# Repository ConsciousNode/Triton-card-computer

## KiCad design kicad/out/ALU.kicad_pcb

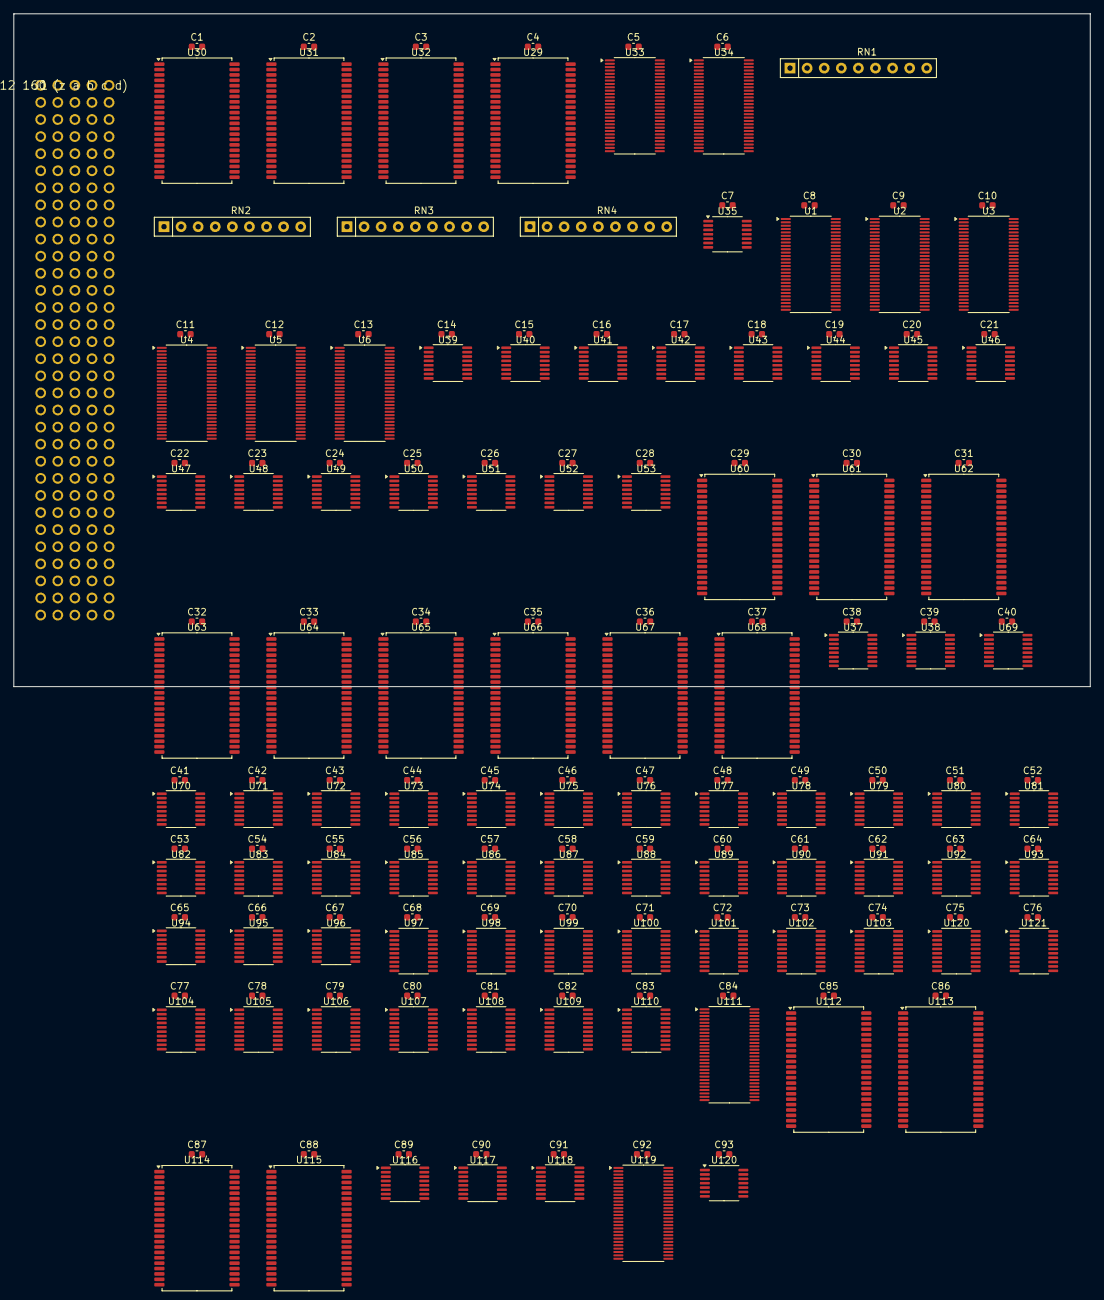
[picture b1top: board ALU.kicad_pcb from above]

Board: 4 copper layers, 160.0 x 100.0 mm, 191 parts (0 on the bottom side), 470 nets, no tracks yet.

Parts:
C1, C2, C3, C4, C5, C6, C7, C8, C9, C10, C11, C12, C13, C14, C15, C16, C17, C18, C19, C20, C21, C22, C23, C24, C25, C26, C27, C28, C29, C30, C31, C32, C33, C34, C35, C36, C37, C38, C39, C40, C41, C42, C43, C44, C45, C46, C47, C48, C49, C50, C51, C52, C53, C54, C55, C56, C57, C58, C59, C60, C61, C62, C63, C64, C65, C66, C67, C68, C69, C70, C71, C72, C73, C74, C75, C76, C77, C78, C79, C80, C81, C82, C83, C84, C85, C86, C87, C88, C89, C90, C91, C92, C93: 100n; C_0603_1608Metric
J1: DIN41612 160 (z a b c d)
RN1, RN2, RN3, RN4: RPACK8; R_Array_SIP9
U1, U2, U3, U4, U5, U6, U33, U34, U111, U119: ALVCH16823; TSSOP-56_6.1x14mm_P0.5mm
U29, U30, U31, U32, U60, U61, U62, U63, U64, U65, U66, U67, U68, U112, U113, U114, U115: IS61WV5128; TSOP-II-44_10.16x18.41mm_P0.8mm
U35: LVC32; TSSOP-14_4.4x5mm_P0.65mm
U37, U39, U40, U69, U116, U117, U118: LVC153; TSSOP-16_4.4x5mm_P0.65mm
U38, U41, U42, U43, U44, U45, U46, U47, U48, U49, U50, U51, U52, U53: LVC157; TSSOP-16_4.4x5mm_P0.65mm
U70, U71, U72, U73, U74, U75, U76, U77, U78, U79, U80, U81, U82, U83, U84, U85, U86, U87, U88, U89, U90, U91, U92, U93, U94, U95, U96: CBTLV3253; TSSOP-16_4.4x5mm_P0.65mm
U97, U98, U99, U100, U101, U102, U103, U120#2, U121: CBTLV3245; TSSOP-20_4.4x6.5mm_P0.65mm
U104, U105, U106, U107, U108, U109, U110: LVC245; TSSOP-20_4.4x6.5mm_P0.65mm
U120: LVC04; TSSOP-14_4.4x5mm_P0.65mm

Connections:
+3V3: C1.1, C2.1, C3.1, C4.1, C5.1, C6.1, C7.1, C8.1, C9.1, C10.1, C11.1, C12.1, C13.1, C14.1, C15.1, C16.1, C17.1, C18.1, C19.1, C20.1, C21.1, C22.1, C23.1, C24.1, C25.1, C26.1, C27.1, C28.1, C29.1, C30.1, C31.1, C32.1, C33.1, C34.1, C35.1, C36.1, C37.1, C38.1, C39.1, C40.1, C41.1, C42.1, C43.1, C44.1, C45.1, C46.1, C47.1, C48.1, C49.1, C50.1, C51.1, C52.1, C53.1, C54.1, C55.1, C56.1, C57.1, C58.1, C59.1, C60.1, C61.1, C62.1, C63.1, C64.1, C65.1, C66.1, C67.1, C68.1, C69.1, C70.1, C71.1, C72.1, C73.1, C74.1, C75.1, C76.1, C77.1, C78.1, C79.1, C80.1, C81.1, C82.1, C83.1, C84.1, C85.1, C86.1, C87.1, C88.1, C89.1, C90.1, C91.1, C92.1, C93.1, J1.z2, J1.z4, J1.z6, J1.z10, J1.z12, J1.z14, J1.z18, J1.z20, J1.z22, J1.z26, J1.z28, J1.z30, RN1.1, RN2.1, RN3.1, RN4.1, U1.1, U1.7, U1.22, U1.28, U1.35, U1.50, U2.1, U2.7, U2.22, U2.28, U2.35, U2.50, U3.1, U3.7, U3.22, U3.28, U3.35, U3.50, U4.1, U4.7, U4.22, U4.28, U4.35, U4.50, U5.1, U5.7, U5.22, U5.28, U5.35, U5.50, U6.1, U6.7, U6.22, U6.28, U6.35, U6.50, U29.11, U29.15, U29.33, U30.11, U30.15, U30.33, U31.11, U31.15, U31.33, U32.11, U32.15, U32.33, U33.1, U33.7, U33.22, U33.28, U33.35, U33.50, U34.1, U34.7, U34.22, U34.28, U34.35, U34.50, U35.14, U37.16, U38.16, U39.4, U39.16, U40.5, U40.15, U40.16, U41.3, U41.6, U41.13, U41.16, U42.16, U43.16, U44.16, U45.16, U46.16, U47.16, U48.16, U49.16, U50.16, U51.16, U52.16, U53.16, U60.11, U60.15, U60.33, U61.11, U61.15, U61.33, U62.11, U62.15, U62.33, U63.11, U63.15, U63.33, U64.11, U64.15, U64.33, U65.11, U65.15, U65.33, U66.11, U66.15, U66.33, U67.11, U67.15, U67.33, U68.11, U68.15, U68.33, U69.16, U70.16, U71.16, U72.16, U73.16, U74.16, U75.16, U76.16, U77.16, U78.16, U79.16, U80.16, U81.16, U82.16, U83.16, U84.16, U85.16, U86.16, U87.16, U88.16, U89.16, U90.16, U91.16, U92.16, U93.16, U94.16, U95.16, U96.16, U97.20, U98.20, U99.20, U100.20, U101.20, U102.20, U103.20, U104.1, U104.20, U105.1, U105.20, U106.1, U106.20, U107.1, U107.20, U108.1, U108.20, U109.1, U109.20, U110.1, U110.20, U111.1, U111.7, U111.22, U111.27, U111.28, U111.30, U111.35, U111.50, U112.11, U112.15, U112.33, U113.11, U113.15, U113.33, U114.11, U114.15, U114.33, U115.11, U115.15, U115.33, U116.16, U117.16, U118.16, U119.1, U119.7, U119.22, U119.28, U119.35, U119.50, U120.14, U120#2.20, U121.20
+5V: J1.z8, J1.z16, J1.z24, J1.z32
/A_LD: U1.30, U1.55, U2.30, U2.55, U3.30, U3.55, U35.3
/B_LD: U4.30, U4.55, U5.30, U5.55, U6.30, U6.55, U35.6
/FL_LD: U35.8, U119.55
A0+: U1.3, U38.3, U60.3
A0-: U1.5, U38.6, U60.4
A1+: U1.6, U60.5
A1-: U1.8, U60.6
A2+: U1.9, U60.7
A2-: U1.10, U60.16
A3+: U1.12, U61.3
A3-: U1.13, U61.4
A4+: U1.14, U61.5
A4-: U1.15, U61.6
A5+: U1.16, U61.7
A5-: U1.17, U61.16
A6+: U1.19, U62.3
A6-: U1.20, U62.4
A7+: U1.21, U62.5
A7-: U1.23, U62.6
A8+: U1.24, U62.7
A8-: U1.26, U62.16
A9+: U2.3, U63.3
A9-: U2.5, U63.4
A10+: U2.6, U63.5
A10-: U2.8, U63.6
A11+: U2.9, U63.7
A11-: U2.10, U63.16
A12+: U2.12, U64.3
A12-: U2.13, U64.4
A13+: U2.14, U64.5
A13-: U2.15, U64.6
A14+: U2.16, U64.7
A14-: U2.17, U64.16
A15+: U2.19, U65.3
A15-: U2.20, U65.4
A16+: U2.21, U65.5
A16-: U2.23, U65.6
A17+: U2.24, U65.7
A17-: U2.26, U65.16
A18+: U3.3, U66.3
A18-: U3.5, U66.4
A19+: U3.6, U66.5
A19-: U3.8, U66.6
A20+: U3.9, U66.7
A20-: U3.10, U66.16
A21+: U3.12, U67.3
A21-: U3.13, U67.4
A22+: U3.14, U67.5
A22-: U3.15, U67.6
A23+: U3.16, U67.7
A23-: U3.17, U67.16
A24+: U3.19, U68.3
A24-: U3.20, U68.4
A25+: U3.21, U68.5
A25-: U3.23, U68.6
A26+: U3.24, U68.7
A26-: U3.26, U68.16
ABORT: J1.c15, U35.2, U35.5, U35.10, U111.55
B0+: U4.3, U42.3, U43.10, U45.3, U46.10, U48.3, U49.10, U51.3, U52.10, U60.17
B0-: U4.5, U42.6, U43.13, U45.6, U46.13, U48.6, U49.13, U51.6, U52.13, U60.18
B1+: U4.6, U42.10, U44.3, U45.10, U47.3, U48.10, U50.3, U51.10, U53.3, U60.19
B1-: U4.8, U42.13, U44.6, U45.13, U47.6, U48.13, U50.6, U51.13, U53.6, U60.20
B2+: U4.9, U43.3, U44.10, U46.3, U47.10, U49.3, U50.10, U52.3, U53.10, U60.26
B2-: U4.10, U43.6, U44.13, U46.6, U47.13, U49.6, U50.13, U52.6, U53.13, U60.27
B3+: U4.12, U42.2
B3-: U4.13, U42.5
B4+: U4.14, U42.11
B4-: U4.15, U42.14
B5+: U4.16, U43.2
B5-: U4.17, U43.5
B6+: U4.19, U43.11
B6-: U4.20, U43.14
B7+: U4.21, U44.2
B7-: U4.23, U44.5
B8+: U4.24, U44.11
B8-: U4.26, U44.14
B9+: U5.3, U45.2
B9-: U5.5, U45.5
B10+: U5.6, U45.11
B10-: U5.8, U45.14
B11+: U5.9, U46.2
B11-: U5.10, U46.5
B12+: U5.12, U46.11
B12-: U5.13, U46.14
B13+: U5.14, U47.2
B13-: U5.15, U47.5
B14+: U5.16, U47.11
B14-: U5.17, U47.14
B15+: U5.19, U48.2
B15-: U5.20, U48.5
B16+: U5.21, U48.11
B16-: U5.23, U48.14
B17+: U5.24, U49.2
B17-: U5.26, U49.5
B18+: U6.3, U49.11
B18-: U6.5, U49.14
B19+: U6.6, U50.2
B19-: U6.8, U50.5
B20+: U6.9, U50.11
B20-: U6.10, U50.14
B21+: U6.12, U51.2
B21-: U6.13, U51.5
B22+: U6.14, U51.11
B22-: U6.15, U51.14
B23+: U6.16, U52.2
B23-: U6.17, U52.5
B24+: U6.19, U52.11
B24-: U6.20, U52.14
B25+: U6.21, U53.2
B25-: U6.23, U53.5
B26+: U6.24, U35.12, U53.11
B26-: U6.26, U35.13, U53.14
BS3+: U42.4, U61.17
BS3-: U42.7, U61.18
BS4+: U42.9, U61.19
BS4-: U42.12, U61.20
BS5+: U43.4, U61.26
BS5-: U43.7, U61.27
BS6+: U43.9, U62.17
BS6-: U43.12, U62.18
BS7+: U44.4, U62.19
BS7-: U44.7, U62.20
BS8+: U44.9, U62.26
BS8-: U44.12, U62.27
BS9+: U45.4, U63.17
BS9-: U45.7, U63.18
BS10+: U45.9, U63.19
BS10-: U45.12, U63.20
BS11+: U46.4, U63.26
BS11-: U46.7, U63.27
BS12+: U46.9, U64.17
BS12-: U46.12, U64.18
BS13+: U47.4, U64.19
BS13-: U47.7, U64.20
BS14+: U47.9, U64.26
BS14-: U47.12, U64.27
BS15+: U48.4, U65.17
BS15-: U48.7, U65.18
BS16+: U48.9, U65.19
BS16-: U48.12, U65.20
BS17+: U49.4, U65.26
BS17-: U49.7, U65.27
BS18+: U49.9, U66.17
BS18-: U49.12, U66.18
BS19+: U50.4, U66.19
BS19-: U50.7, U66.20
BS20+: U50.9, U66.26
BS20-: U50.12, U66.27
BS21+: U51.4, U67.17
BS21-: U51.7, U67.18
BS22+: U51.9, U67.19
BS22-: U51.12, U67.20
BS23+: U52.4, U67.26
BS23-: U52.7, U67.27
BS24+: U52.9, U68.17
BS24-: U52.12, U68.18
BS25+: U53.4, U68.19
BS25-: U53.7, U68.20
BS26+: U53.9, U68.26
BS26-: U53.12, U68.27
BTOPNZ: J1.c31, U35.11
C0+: U39.7, U60.28
C0-: U39.9, U60.29
C1+: U60.35, U61.28
C1-: U60.36, U61.29
C2+: U61.35, U62.28
C2-: U61.36, U62.29
C3+: U62.35, U63.28
C3-: U62.36, U63.29
C4+: U63.35, U64.28
C4-: U63.36, U64.29
C5+: U64.35, U65.28
C5-: U64.36, U65.29
C6+: U65.35, U66.28
C6-: U65.36, U66.29
C7+: U66.35, U67.28
C7-: U66.36, U67.29
C8+: U67.35, U68.28
C8-: U67.36, U68.29
C9+: U68.35, U69.5, U115.29
C9-: U68.36, U69.11, U115.30
CF+: J1.c27, U39.5, U119.6, U119.40
CF-: J1.c28, U39.11, U119.8, U119.38
CLK: J1.c10, U1.29, U1.56, U2.29, U2.56, U3.29, U3.56, U4.29, U4.56, U5.29, U5.56, U6.29, U6.56, U33.29, U33.56, U34.29, U34.56, U111.29, U111.56, U119.29, U119.56
CSD0: U30.9, U33.54
CSD1: U30.10, U33.52
CSD2: U30.13, U33.51
CSD3: U30.14, U33.49
CSD4: U30.31, U33.48
CSD5: U30.32, U33.47
CSD6: U30.35, U33.45
CSD7: U30.36, U33.44
CSD8: U31.9, U33.43
CSD9: U31.10, U33.42
CSD10: U31.13, U33.41
CSD11: U31.14, U33.40
CSD12: U31.31, U33.38
CSD13: U31.32, U33.37
CSD14: U31.35, U33.36
CSD15: U31.36, U33.34
CSD16: U32.9, U33.33
CSD17: U32.10, U33.31
CSD18: U32.13, U34.54
CSD19: U32.14, U34.52
CSD20: U32.31, U34.51
CSD21: U32.32, U34.49
CSD22: U32.35, U34.48
CSD23: U32.36, U34.47
CSD24: U29.9, U34.45
CSD25: U29.10, U34.44
CSD26: U29.13, U34.43
CSD27: U29.14, U34.42
CSD28: U29.31, U34.41
CSD29: U29.32, U34.40
CSD30: U29.35, U34.38
CSD31: U29.36, U34.37
CW_/A_CE: RN1.2, U33.3, U35.1
CW_/BUSOE: RN3.7, U34.8, U104.19, U105.19, U106.19, U107.19, U108.19, U109.19, U110.19
CW_/B_CE: RN1.3, U33.5, U35.4
CW_/ESRV: RN4.8, U34.19, U120#2.19, U121.19
CW_/FL_CE: RN3.8, U34.9, U35.9
CW_/L9OE: RN2.8, U33.21, U97.19, U98.19, U99.19, U100.19, U101.19, U102.19, U103.19
CW_/SHOE: RN2.7, U33.20, U75.1, U75.15, U76.1, U76.15, U77.1, U77.15, U78.1, U78.15, U79.1, U79.15, U80.1, U80.15, U81.1, U81.15, U82.1, U82.15, U83.1, U83.15, U84.1, U84.15, U85.1, U85.15, U86.1, U86.15, U87.1, U87.15, U88.1, U88.15, U89.1, U89.15, U90.1, U90.15, U91.1, U91.15, U92.1, U92.15, U93.1, U93.15, U94.1, U94.15, U95.1, U95.15, U96.1, U96.15
CW_/SHOE_LO: RN4.7, U34.17, U70.1, U70.15, U71.1, U71.15, U72.1, U72.15, U73.1, U73.15, U74.1, U74.15
CW_/SH_CE: RN3.9, U34.10, U119.30
CW_/STR: RN4.9, U34.20, U120.1
CW_BCAST: RN2.4, U33.16, U42.1, U43.1, U44.1, U45.1, U46.1, U47.1, U48.1, U49.1, U50.1, U51.1, U52.1, U53.1
CW_CIN0: RN2.2, U33.14, U39.14
CW_CIN1: RN2.3, U33.15, U39.2
CW_FILL0: RN2.9, U33.23, U69.14
CW_FILL1: RN3.2, U33.24, U69.2
CW_FN0: RN1.4, U33.6, U41.2, U60.30, U61.30, U62.30
CW_FN1: RN1.5, U33.8, U41.5, U60.38, U61.38, U62.38
CW_FN2: RN1.6, U33.9, U41.11, U60.39, U61.39, U62.39
CW_FN3: RN1.7, U33.10, U41.14, U60.40, U61.40, U62.40
CW_FOP0: RN4.4, U34.14, U115.3
CW_FOP1: RN4.5, U34.15, U115.4
CW_FOP2: RN4.6, U34.16, U115.5
CW_FSEL0: RN4.2, U34.12, U116.14, U117.14, U118.14
CW_FSEL1: RN4.3, U34.13, U116.2, U117.2, U118.2
CW_LDQT: RN3.5, U34.5, U38.1
CW_LINK0: RN3.3, U33.26, U37.14
CW_LINK1: RN3.4, U34.3, U37.2
CW_NEG0: RN1.8, U33.12, U40.14
CW_NEG1: RN1.9, U33.13, U40.2
CW_SHS0: RN2.5, U33.17, U70.14, U71.14, U72.14, U73.14, U74.14, U75.14, U76.14, U77.14, U78.14, U79.14, U80.14, U81.14, U82.14, U83.14, U84.14, U85.14, U86.14, U87.14, U88.14, U89.14, U90.14, U91.14, U92.14, U93.14, U94.14, U95.14, U96.14
CW_SHS1: RN2.6, U33.19, U70.2, U71.2, U72.2, U73.2, U74.2, U75.2, U76.2, U77.2, U78.2, U79.2, U80.2, U81.2, U82.2, U83.2, U84.2, U85.2, U86.2, U87.2, U88.2, U89.2, U90.2, U91.2, U92.2, U93.2, U94.2, U95.2, U96.2
CW_W9: RN3.6, U34.6, U41.1
D0+: J1.a1, U1.54, U4.54, U104.18, U112.3, U116.4
D0-: J1.a2, U1.52, U4.52, U104.17, U112.4, U116.12
D1+: J1.a3, U1.51, U4.51, U104.16, U112.5, U117.4
D1-: J1.a4, U1.49, U4.49, U104.15, U112.6, U117.12
D2+: J1.a5, U1.48, U4.48, U104.14, U112.7, U118.4
D2-: J1.a6, U1.47, U4.47, U104.13, U112.16, U118.12
D3+: J1.a7, U1.45, U4.45, U104.12, U112.17
D3-: J1.a9, U1.44, U4.44, U104.11, U112.18
D4+: J1.a10, U1.43, U4.43, U105.18, U112.19
D4-: J1.a11, U1.42, U4.42, U105.17, U112.20
D5+: J1.a12, U1.41, U4.41, U105.16, U112.26
D5-: J1.a13, U1.40, U4.40, U105.15, U112.27
D6+: J1.a14, U1.38, U4.38, U105.14, U112.28
D6-: J1.a15, U1.37, U4.37, U105.13, U112.29
D7+: J1.a17, U1.36, U4.36, U105.12, U112.30
D7-: J1.a18, U1.34, U4.34, U105.11, U112.38
D8+: J1.a19, U1.33, U4.33, U106.18, U112.39
D8-: J1.a20, U1.31, U4.31, U106.17, U112.40
D9+: J1.a21, U2.54, U5.54, U106.16, U113.3
D9-: J1.a22, U2.52, U5.52, U106.15, U113.4
D10+: J1.a23, U2.51, U5.51, U106.14, U113.5
D10-: J1.a25, U2.49, U5.49, U106.13, U113.6
D11+: J1.a26, U2.48, U5.48, U106.12, U113.7
D11-: J1.a27, U2.47, U5.47, U106.11, U113.16
D12+: J1.a28, U2.45, U5.45, U107.18, U113.17
D12-: J1.a29, U2.44, U5.44, U107.17, U113.18
D13+: J1.a30, U2.43, U5.43, U107.16, U113.19
D13-: J1.a31, U2.42, U5.42, U107.15, U113.20
D14+: J1.b1, U2.41, U5.41, U107.14, U113.26
D14-: J1.b2, U2.40, U5.40, U107.13, U113.27
D15+: J1.b3, U2.38, U5.38, U107.12, U113.28
D15-: J1.b4, U2.37, U5.37, U107.11, U113.29
D16+: J1.b5, U2.36, U5.36, U108.18, U113.30
D16-: J1.b6, U2.34, U5.34, U108.17, U113.38
D17+: J1.b7, U2.33, U5.33, U108.16, U113.39
D17-: J1.b9, U2.31, U5.31, U108.15, U113.40
D18+: J1.b10, U3.54, U6.54, U108.14, U114.3
D18-: J1.b11, U3.52, U6.52, U108.13, U114.4
D19+: J1.b12, U3.51, U6.51, U108.12, U114.5
D19-: J1.b13, U3.49, U6.49, U108.11, U114.6
D20+: J1.b14, U3.48, U6.48, U109.18, U114.7
D20-: J1.b15, U3.47, U6.47, U109.17, U114.16
D21+: J1.b17, U3.45, U6.45, U109.16, U114.17
D21-: J1.b18, U3.44, U6.44, U109.15, U114.18
D22+: J1.b19, U3.43, U6.43, U109.14, U114.19
D22-: J1.b20, U3.42, U6.42, U109.13, U114.20
D23+: J1.b21, U3.41, U6.41, U109.12, U114.26
D23-: J1.b22, U3.40, U6.40, U109.11, U114.27
D24+: J1.b23, U3.38, U6.38, U110.18, U114.28
D24-: J1.b25, U3.37, U6.37, U110.17, U114.29
D25+: J1.b26, U3.36, U6.36, U110.16, U114.30
D25-: J1.b27, U3.34, U6.34, U110.15, U114.38
D26+: J1.b28, U3.33, U6.33, U110.14, U114.39
D26-: J1.b29, U3.31, U6.31, U110.13, U114.40
FILL+: U69.7, U96.4
FILL-: U69.9, U96.12
FNU0: U41.4, U63.30, U64.30, U65.30, U66.30, U67.30, U68.30
FNU1: U41.7, U63.38, U64.38, U65.38, U66.38, U67.38, U68.38
FNU2: U41.9, U63.39, U64.39, U65.39, U66.39, U67.39, U68.39
FNU3: U41.12, U63.40, U64.40, U65.40, U66.40, U67.40, U68.40
GND: C1.2, C2.2, C3.2, C4.2, C5.2, C6.2, C7.2, C8.2, C9.2, C10.2, C11.2, C12.2, C13.2, C14.2, C15.2, C16.2, C17.2, C18.2, C19.2, C20.2, C21.2, C22.2, C23.2, C24.2, C25.2, C26.2, C27.2, C28.2, C29.2, C30.2, C31.2, C32.2, C33.2, C34.2, C35.2, C36.2, C37.2, C38.2, C39.2, C40.2, C41.2, C42.2, C43.2, C44.2, C45.2, C46.2, C47.2, C48.2, C49.2, C50.2, C51.2, C52.2, C53.2, C54.2, C55.2, C56.2, C57.2, C58.2, C59.2, C60.2, C61.2, C62.2, C63.2, C64.2, C65.2, C66.2, C67.2, C68.2, C69.2, C70.2, C71.2, C72.2, C73.2, C74.2, C75.2, C76.2, C77.2, C78.2, C79.2, C80.2, C81.2, C82.2, C83.2, C84.2, C85.2, C86.2, C87.2, C88.2, C89.2, C90.2, C91.2, C92.2, C93.2, J1.a8, J1.a16, J1.a24, J1.a32, J1.b8, J1.b16, J1.b24, J1.b32, J1.c8, J1.c16, J1.c24, J1.c32, J1.d8, J1.d16, J1.d24, J1.d32, J1.z1, J1.z3, J1.z5, J1.z7, J1.z9, J1.z11, J1.z13, J1.z15, J1.z17, J1.z19, J1.z21, J1.z23, J1.z25, J1.z27, J1.z29, J1.z31, U1.2, U1.4, U1.11, U1.18, U1.25, U1.27, U1.32, U1.39, U1.46, U1.53, U2.2, U2.4, U2.11, U2.18, U2.25, U2.27, U2.32, U2.39, U2.46, U2.53, U3.2, U3.4, U3.11, U3.18, U3.25, U3.27, U3.32, U3.39, U3.46, U3.53, U4.2, U4.4, U4.11, U4.18, U4.25, U4.27, U4.32, U4.39, U4.46, U4.53, U5.2, U5.4, U5.11, U5.18, U5.25, U5.27, U5.32, U5.39, U5.46, U5.53, U6.2, U6.4, U6.11, U6.18, U6.25, U6.27, U6.32, U6.39, U6.46, U6.53, U29.8, U29.12, U29.26, U29.27, U29.28, U29.29, U29.30, U29.34, U29.37, U29.38, U29.39, U29.40, U29.41, U30.8, U30.12, U30.26, U30.27, U30.28, U30.29, U30.30, U30.34, U30.37, U30.38, U30.39, U30.40, U30.41, U31.8, U31.12, U31.26, U31.27, U31.28, U31.29, U31.30, U31.34, U31.37, U31.38, U31.39, U31.40, U31.41, U32.8, U32.12, U32.26, U32.27, U32.28, U32.29, U32.30, U32.34, U32.37, U32.38, U32.39, U32.40, U32.41, U33.4, U33.11, U33.18, U33.25, U33.30, U33.32, U33.39, U33.46, U33.53, U33.55, U34.4, U34.11, U34.18, U34.25, U34.30, U34.31, U34.32, U34.33, U34.34, U34.36, U34.39, U34.46, U34.53, U34.55, U35.7, U37.1, U37.3, U37.8, U37.13, U37.15, U38.8, U38.10, U38.11, U38.13, U38.14, U38.15, U39.1, U39.6, U39.8, U39.10, U39.12, U39.15, U40.1, U40.3, U40.6, U40.8, U40.10, U40.11, U40.12, U40.13, U41.8, U41.10, U41.15, U42.8, U42.15, U43.8, U43.15, U44.8, U44.15, U45.8, U45.15, U46.8, U46.15, U47.8, U47.15, U48.8, U48.15, U49.8, U49.15, U50.8, U50.15, U51.8, U51.15, U52.8, U52.15, U53.8, U53.15, U60.8, U60.12, U60.34, U60.37, U61.8, U61.12, U61.34, U61.37, U62.8, U62.12, U62.34, U62.37, U63.8, U63.12, U63.34, U63.37, U64.8, U64.12, U64.34, U64.37, U65.8, U65.12, U65.34, U65.37, U66.8, U66.12, U66.34, U66.37, U67.8, U67.12, U67.34, U67.37, U68.8, U68.12, U68.34, U68.37, U69.1, U69.3, U69.6, U69.8, U69.10, U69.13, U69.15, U70.5, U70.8, U70.11, U71.8, U72.8, U73.8, U74.8, U75.8, U76.8, U77.8, U78.8, U79.8, U80.8, U81.8, U82.8, U83.8, U84.8, U85.8, U86.8, U87.8, U88.3, U88.8, U88.13, U89.3, U89.8, U89.13, U90.3, U90.8, U90.13, U91.3, U91.8, U91.13, U92.3, U92.8, U92.13, U93.3, U93.8, U93.13, U94.3, U94.8, U94.13, U95.3, U95.8, U95.13, U96.3, U96.8, U96.13, U97.2, U97.3, U97.4, U97.5, U97.6, U97.7, U97.8, U97.9, U97.10, U98.2, U98.3, U98.4, U98.5, U98.6, U98.7, U98.8, U98.9, U98.10, U99.2, U99.3, U99.10, U100.10, U101.10, U102.10, U103.8, U103.9, U103.10, U104.10, U105.10, U106.10, U107.10, U108.10, U109.10, U110.8, U110.9, U110.10, U111.2, U111.4, U111.11, U111.18, U111.25, U111.31, U111.32, U111.33, U111.34, U111.36, U111.37, U111.38, U111.39, U111.40, U111.41, U111.42, U111.43, U111.44, U111.45, U111.46, U111.47, U111.48, U111.53, U112.8, U112.12, U112.34, U112.37, U112.41, U113.8, U113.12, U113.34, U113.37, U113.41, U114.8, U114.12, U114.34, U114.37, U114.41, U115.8, U115.12, U115.34, U115.37, U115.40, U115.41, U116.1, U116.3, U116.8, U116.13, U116.15, U117.1, U117.3, U117.8, U117.13, U117.15, U118.1, U118.3, U118.8, U118.13, U118.15, U119.2, U119.4, U119.11, U119.18, U119.25, U119.27, U119.31, U119.32, U119.33, U119.34, U119.39, U119.43, U119.44, U119.45, U119.46, U119.53, U120.3, U120.5, U120.7, U120.9, U120.11, U120.13, U120#2.9, U120#2.10, U121.3, U121.4, U121.5, U121.6, U121.7, U121.8, U121.9, U121.10
IE: J1.d26, U121.2
LINK+: U37.6, U39.3, U69.4, U111.3
LINK-: U37.10, U39.13, U69.12, U111.5
LN+: U37.7, U111.54, U115.38
LN-: U37.9, U111.52, U115.39
NCF+: U117.7, U119.51
NCF-: U117.9, U119.49
NEG: U40.7, U60.41, U61.41, U62.41, U63.41, U64.41, U65.41, U66.41, U67.41, U68.41
NOF+: U118.7, U119.48
NOF-: U118.9, U119.47
NSF+: U116.7, U119.54
NSF-: U116.9, U119.52
OF+: U115.16, U119.9, U119.37
OF-: U115.17, U119.10, U119.36
PRIV: J1.d25, U120#2.8
QN+: U38.4, U111.51
QN-: U38.7, U111.49
QT+: J1.c29, U38.2, U111.6
QT-: J1.c30, U38.5, U40.4, U111.8
R0+: U37.5, U60.9, U70.6, U71.5, U99.4
R0-: U37.11, U60.10, U70.10, U71.11, U99.5
R1+: U60.13, U70.4, U71.6, U72.5, U99.6
R1-: U60.14, U70.12, U71.10, U72.11, U99.7
R2+: U60.31, U71.4, U72.6, U73.5, U99.8
R2-: U60.32, U71.12, U72.10, U73.11, U99.9
R3+: U61.9, U72.4, U73.6, U74.5, U100.2
R3-: U61.10, U72.12, U73.10, U74.11, U100.3
R4+: U61.13, U73.4, U74.6, U75.5, U100.4
R4-: U61.14, U73.12, U74.10, U75.11, U100.5
R5+: U61.31, U74.4, U75.6, U76.5, U100.6
R5-: U61.32, U74.12, U75.10, U76.11, U100.7
R6+: U62.9, U75.4, U76.6, U77.5, U100.8
R6-: U62.10, U75.12, U76.10, U77.11, U100.9
R7+: U62.13, U76.4, U77.6, U78.5, U101.2
R7-: U62.14, U76.12, U77.10, U78.11, U101.3
R8+: U62.31, U77.4, U78.6, U79.5, U101.4
R8-: U62.32, U77.12, U78.10, U79.11, U101.5
R9+: U63.9, U70.3, U78.4, U79.6, U80.5, U101.6
R9-: U63.10, U70.13, U78.12, U79.10, U80.11, U101.7
R10+: U63.13, U71.3, U79.4, U80.6, U81.5, U101.8
R10-: U63.14, U71.13, U79.12, U80.10, U81.11, U101.9
R11+: U63.31, U72.3, U80.4, U81.6, U82.5, U102.2
R11-: U63.32, U72.13, U80.12, U81.10, U82.11, U102.3
R12+: U64.9, U73.3, U81.4, U82.6, U83.5, U102.4
R12-: U64.10, U73.13, U81.12, U82.10, U83.11, U102.5
R13+: U64.13, U74.3, U82.4, U83.6, U84.5, U102.6
R13-: U64.14, U74.13, U82.12, U83.10, U84.11, U102.7
R14+: U64.31, U75.3, U83.4, U84.6, U85.5, U102.8
R14-: U64.32, U75.13, U83.12, U84.10, U85.11, U102.9
R15+: U65.9, U76.3, U84.4, U85.6, U86.5, U103.2
R15-: U65.10, U76.13, U84.12, U85.10, U86.11, U103.3
R16+: U65.13, U77.3, U85.4, U86.6, U87.5, U103.4
R16-: U65.14, U77.13, U85.12, U86.10, U87.11, U103.5
R17+: U65.31, U78.3, U86.4, U87.6, U88.5, U103.6
R17-: U65.32, U78.13, U86.12, U87.10, U88.11, U103.7
R18+: U66.9, U79.3, U87.4, U88.6, U89.5
R18-: U66.10, U79.13, U87.12, U88.10, U89.11
R19+: U66.13, U80.3, U88.4, U89.6, U90.5
R19-: U66.14, U80.13, U88.12, U89.10, U90.11
R20+: U66.31, U81.3, U89.4, U90.6, U91.5
R20-: U66.32, U81.13, U89.12, U90.10, U91.11
R21+: U67.9, U82.3, U90.4, U91.6, U92.5
R21-: U67.10, U82.13, U90.12, U91.10, U92.11
R22+: U67.13, U83.3, U91.4, U92.6, U93.5
R22-: U67.14, U83.13, U91.12, U92.10, U93.11
R23+: U67.31, U84.3, U92.4, U93.6, U94.5
R23-: U67.32, U84.13, U92.12, U93.10, U94.11
R24+: U68.9, U85.3, U93.4, U94.6, U95.5
R24-: U68.10, U85.13, U93.12, U94.10, U95.11
R25+: U68.13, U86.3, U94.4, U95.6, U96.5
R25-: U68.14, U86.13, U94.12, U95.10, U96.11
R26+: U37.4, U68.31, U87.3, U95.4, U96.6
R26-: U37.12, U68.32, U87.13, U95.12, U96.10
RESET: J1.c12, U33.2, U33.27, U34.2, U34.27
S0+: U70.7, U97.18, U104.2, U120#2.18
S0-: U70.9, U97.17, U104.3, U120#2.17
S1+: U71.7, U97.16, U104.4, U120#2.16
S1-: U71.9, U97.15, U104.5, U120#2.15
S2+: U72.7, U97.14, U104.6, U120#2.14
S2-: U72.9, U97.13, U104.7, U120#2.13
S3+: U73.7, U97.12, U104.8, U120#2.12
S3-: U73.9, U97.11, U104.9, U120#2.11
S4+: U74.7, U98.18, U105.2, U121.18
S4-: U74.9, U98.17, U105.3, U121.17
S5+: U75.7, U98.16, U105.4
S5-: U75.9, U98.15, U105.5
S6+: U76.7, U98.14, U105.6
S6-: U76.9, U98.13, U105.7
S7+: U77.7, U98.12, U105.8
S7-: U77.9, U98.11, U105.9
S8+: U78.7, U99.18, U106.2
S8-: U78.9, U99.17, U106.3
S9+: U79.7, U99.16, U106.4
S9-: U79.9, U99.15, U106.5
S10+: U80.7, U99.14, U106.6
S10-: U80.9, U99.13, U106.7
S11+: U81.7, U99.12, U106.8
S11-: U81.9, U99.11, U106.9
S12+: U82.7, U100.18, U107.2
S12-: U82.9, U100.17, U107.3
S13+: U83.7, U100.16, U107.4
S13-: U83.9, U100.15, U107.5
S14+: U84.7, U100.14, U107.6
S14-: U84.9, U100.13, U107.7
S15+: U85.7, U100.12, U107.8
S15-: U85.9, U100.11, U107.9
S16+: U86.7, U101.18, U108.2
S16-: U86.9, U101.17, U108.3
S17+: U87.7, U101.16, U108.4
S17-: U87.9, U101.15, U108.5
S18+: U88.7, U101.14, U108.6
S18-: U88.9, U101.13, U108.7
S19+: U89.7, U101.12, U108.8
S19-: U89.9, U101.11, U108.9
S20+: U90.7, U102.18, U109.2
S20-: U90.9, U102.17, U109.3
S21+: U91.7, U102.16, U109.4
S21-: U91.9, U102.15, U109.5
S22+: U92.7, U102.14, U109.6
S22-: U92.9, U102.13, U109.7
S23+: U93.7, U102.12, U109.8
S23-: U93.9, U102.11, U109.9
S24+: U94.7, U103.18, U110.2
S24-: U94.9, U103.17, U110.3
S25+: U95.7, U103.16, U110.4
S25-: U95.9, U103.15, U110.5
S26+: U96.7, U103.14, U110.6
S26-: U96.9, U103.13, U110.7
SCF+: U117.5, U119.17, U120#2.4
SCF-: U117.11, U119.19, U120#2.5
SF+: J1.c25, U115.6, U119.3, U119.42
SF-: J1.c26, U115.7, U119.5, U119.41
SOF+: U118.5, U119.20, U120#2.6
SOF-: U118.11, U119.21, U120#2.7
SSF+: U116.5, U119.15, U120#2.2
SSF-: U116.11, U119.16, U120#2.3
STRETCH: J1.c14, U120.2
TCF+: U115.13, U117.6
TCF-: U115.14, U117.10
TOF+: U115.31, U118.6
TOF-: U115.32, U118.10
TS0+: U112.9, U115.18
TS0-: U112.10, U115.19
TS1+: U113.9, U115.20
TS1-: U113.10, U115.26
TS2+: U114.9, U115.27
TS2-: U114.10, U115.28
TSF+: U115.9, U116.6
TSF-: U115.10, U116.10
UA0: J1.b30, U29.3, U30.3, U31.3, U32.3
UA1: J1.b31, U29.4, U30.4, U31.4, U32.4
UA2: J1.c1, U29.5, U30.5, U31.5, U32.5
UA3: J1.c2, U29.6, U30.6, U31.6, U32.6
UA4: J1.c3, U29.7, U30.7, U31.7, U32.7
UA5: J1.c4, U29.16, U30.16, U31.16, U32.16
UA6: J1.c5, U29.17, U30.17, U31.17, U32.17
UA7: J1.c6, U29.18, U30.18, U31.18, U32.18
UA8: J1.c7, U29.19, U30.19, U31.19, U32.19
UA9: J1.c9, U29.20, U30.20, U31.20, U32.20
